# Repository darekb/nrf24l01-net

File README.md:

#branch test01

in this branch i test comunication via different pipe for each sensors.

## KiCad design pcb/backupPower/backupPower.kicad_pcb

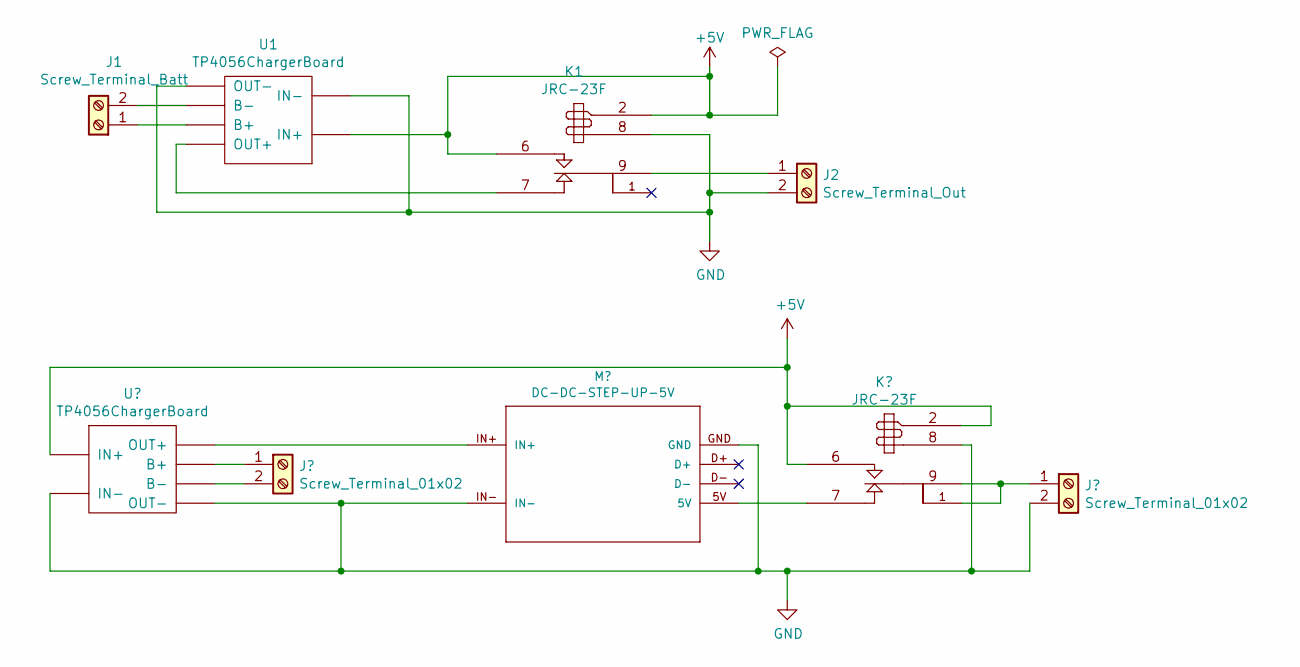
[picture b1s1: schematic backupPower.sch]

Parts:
J1: Screw_Terminal_Batt; mors_2p
J2: Screw_Terminal_Out; mors_2p
K1: JRC-23F
U1: TP4056ChargerBoard; TP4056ChargingBoard

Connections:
+5V: K1.2, K1.6, U1.IN+
GND: J2.2, K1.8, U1.IN-, U1.OUT-
unnamed: J1.1, U1.B+
unnamed: J1.2, U1.B-
unnamed: J2.1, K1.9
unnamed: K1.7, U1.OUT+

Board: 2 copper layers, 4 parts (0 on the bottom side), 6 nets, no tracks yet.

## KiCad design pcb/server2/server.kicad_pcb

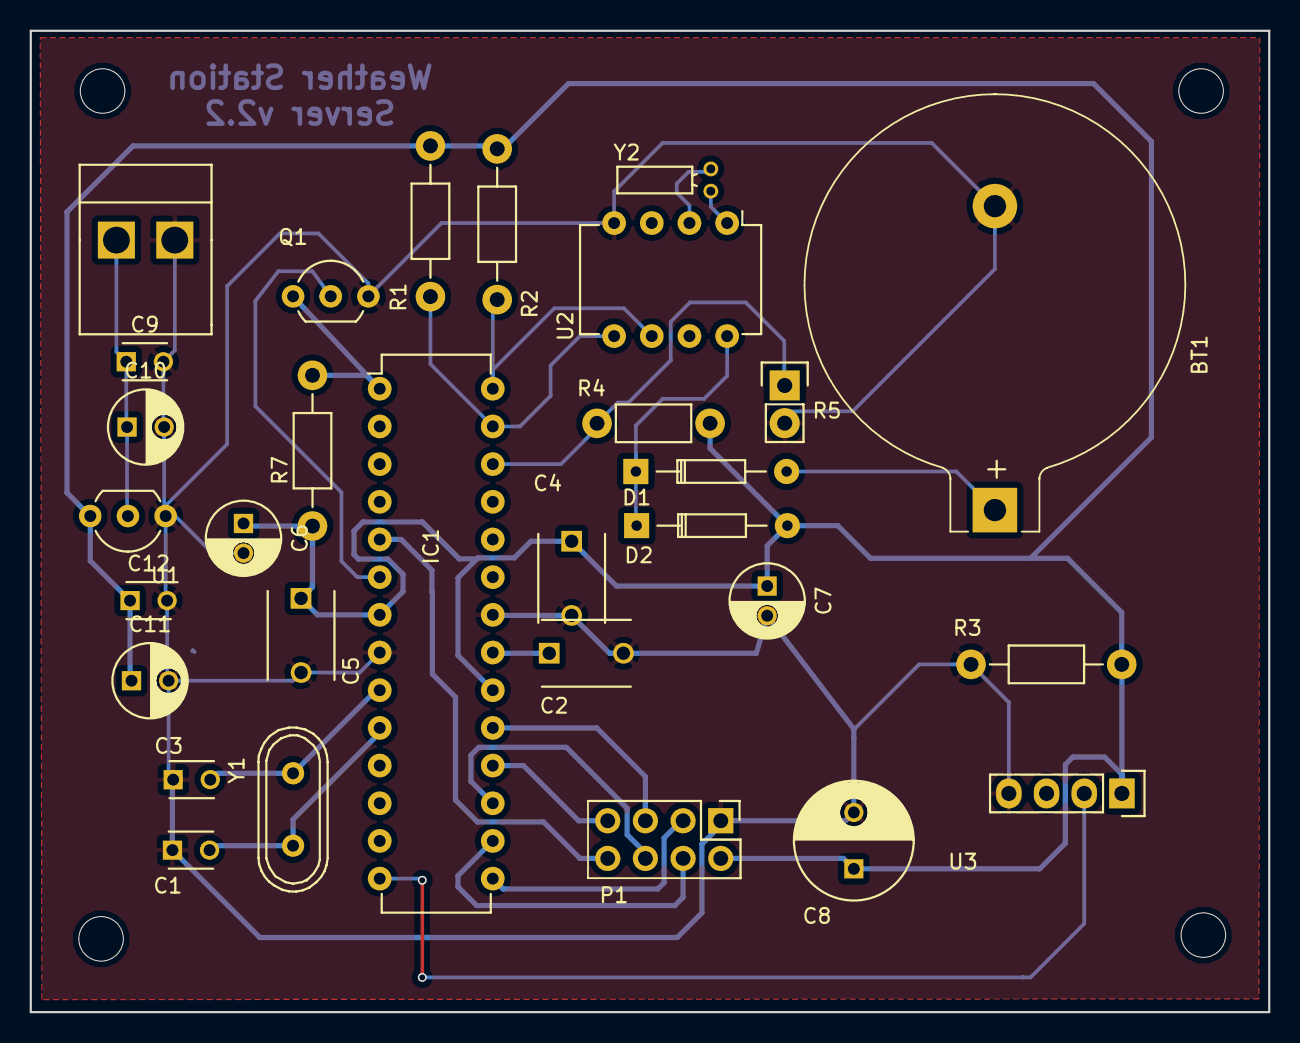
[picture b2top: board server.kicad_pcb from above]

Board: 2 copper layers, 83.5 x 66.2 mm, 30 parts (0 on the bottom side), 22 nets.

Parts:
BT1: Battery; BatteryHolder_Keystone_104_1x23mm
C1, C3: 22p; C_Disc_D3_P2.5
C2, C4, C5: 100n; C_Disc_D6_P5
C6, C7: 10u; C_Radial_D5_L11_P2
C8: 470u; C_Radial_D8_L13_P3.8
C9, C12: 100n; C_Disc_D3_P2.5
C10, C11: 10u; C_Radial_D5_L6_P2.5
D1, D2: 1N4148; Diode_DO-35_SOD27_Horizontal_RM10
IC1: ATMEGA328P-P; DIP-28_W7.62mm
P1: nRF24L01; Socket_Strip_Straight_2x04_Pitch2.54mm
P3: CONN_01X02; GTK2400-V2
Q1: BC548; TO-92_Inline_Wide
R1, R2: 4k7; Resistor_Horizontal_RM10mm
R3: 5k1; Resistor_Horizontal_RM10mm
R4: 12k; Resistor_Horizontal_RM7mm
R5: 5k-10k; Pin_Header_Straight_1x02
R7: 10k; Resistor_Horizontal_RM10mm
U1: HT7333; TO-92_Inline_Wide
U2: PCF8563; DIP-8_W7.62mm
U3: DHT11; DHT22_Temperature_Humidity
Y1: 8Mhz; Crystal_HC49-U_Vertical
Y2: 32.768kHz; Crystal_Round_Horizontal_2mm

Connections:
+3V3: C4.1, C5.1, C6.1, C7.1, C8.1, C11.1, C12.1, D2.2, IC1.7, IC1.20, P1.2, R1.1, R2.1, R3.1, R4.1, R7.1, U1.3, U3.1
ADC3: IC1.26, R4.2, R5.1
CE: IC1.15, P1.3
CSN: IC1.16, P1.4
GND: BT1.2, C1.1, C2.2, C3.1, C4.2, C5.2, C6.2, C7.2, C8.2, C9.2, C10.2, C11.2, C12.2, IC1.8, IC1.22, P1.1, P3.1, Q1.3, R3.2, R5.2, U1.1, U2.4, U3.4
INT1: IC1.5, P1.8
MISO: IC1.18, P1.7
MOSI: IC1.17, P1.6
unnamed: BT1.1, D1.2
unnamed: C2.1, IC1.21
unnamed: C9.1, C10.1, P3.2, U1.2
unnamed: D1.1, D2.1, U2.8
unnamed: U2.1, Y2.1
unnamed: U2.2, Y2.2
PB0: IC1.14, U3.2
PD4: IC1.6, Q1.2
RESET: IC1.1, Q1.1, R7.2
SCK: IC1.19, P1.5
SCL: IC1.28, R2.2, U2.6
SDA: IC1.27, R1.2, U2.5
XTAL1: C3.2, IC1.9, Y1.1
XTAL2: C1.2, IC1.10, Y1.2

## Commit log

2017-05-07 start
2017-05-07 add readme
2017-05-09 workin solution (not very well but ok)
2017-05-10 working solutiion 1 pipe differents adresses
2017-05-10 workin solution
2017-05-11 all it is ok
2017-05-12 more tests
2017-05-24 working solution
2017-05-31 all ok
2017-06-01 remove float to decrease kode size
2017-06-24 new version with atmega8 as sensors and atmega328 as server
2017-07-07 propably work (not tested)
2017-10-31 change nrf24 conigurartion
2018-01-02 a lot changes
2018-01-03 working solution (get measurements, reset after 3 fails, get data from server)
2018-01-04 new version of server and sensor21
2018-01-05 add circuit scheme and pcb project in KiCad
2018-01-16 łączy co dugie wywołanie
2018-01-16 clean code
2018-01-16 after cleaning code
2018-01-17 test
2018-01-17 asdf
2018-01-22 some changes
2018-01-23 add interupt on error sending data from NRF24L01
2018-01-23 sme changes
2018-01-23 nic nie działa
2018-01-24 działa co drugie wysłanie
2018-01-24 test01
2018-01-29 not work
2018-01-29 log file
2018-01-29 workin partly
2018-02-01 working almost well
2018-02-02 clean some code
2018-02-05 all works ok
2018-02-07 server side work fine
2018-02-08 all worl well
2018-02-15 all work well
2018-02-19 add slPCF8563.c slPCF8563.h and registers mnemonics
2018-02-19 add controls status bits mnemonics
2018-02-19 library PCF8563 writed but not tested yet
2018-02-20 some mesurements
2019-04-04 before big changes
